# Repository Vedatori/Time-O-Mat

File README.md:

# Time-O-Mat [cz]
Time-O-Mat jsou hodiny navržené pro Letní robotický tábor 2022 organizovaný spolkem [Vědátoři](vedatori.com). Jedná se o otevřenou platformu, která si klade za cíle zlepšit dovednosti při mechanické stavbě a pájení. Účastníci dostali tento výrobek jako stavebnici, kdy z předem připravených dílů sestavili mechanickou část a poté pájeli nestandardní součástky na DPS s předem osazenými SMD součástkami. Po finalizaci je možné hodiny naprogramovat a používat pro zlepšení schopností algoritmizace a programování účastníků díky možnostem, které poskytují vsupní a výstupní periferie.

Mechanickou část lze rozdělit na dvě hlavní části - krabici a osmičky (segmentové zobrazovače). Vnější části krabice jsou vyřezány z překližky na laserové řezačce a obsahují zámkové západky. Ty se při stavbě lepí disperzním lepidlem a po vyschnutí tvoří pevný základ pro uložení ostatních dílů. Pouze horní část je odnímatelná a připevněná šrouby, které jsou schované v podpůrných 3D tištěných dílech, aby nekazily estetický dojem. Základní díl osmiček a dvojtečky je vytisknutý na 3D tiskárně a difuzery jednotlivých segmentů vyřezané z mléčného plexiskla se do něj vkládají z vnitřní strany a jsou uchyceny pomocí západek. Spojení osmiček a krabice zajišťuje 3D tištěný nosník umístěný uvnitř krabice, který také fixuje desky plošných spojů (DPS).

Hlavní DPS obsahuje zejména mikrokontroler ESP32, který je na ni připájen. Programování a napájení je zajištěno přes USB C. Hlavní DPS obsahuje také tlačítka, fotorezistory, bzučák a teplotní senzor. Do horního krytu je vsazena tenká podlouhlá DPS, která slouží jako senzor s osmi kapacitními tlačítky. Dominantou tohoto zařízení jsou DPS ve tvaru osmiček a dvojtečky, které jsou vsazeny za difuzery. Za každým segmentem jsou umístěny tři adresovatelné RGB LED. Další takové LED jsou umístěny zezadu na LED pásku, který zajišťuje ambientní podsvětlení prostoru za výrobkem. Hodiny jsou rozebiratelné, jednotlivé DPS jsou spojeny konektory, vzdálenější periferie pomocí kabelů.

Všechny periferie byly zvoleny tak, aby vytvořily hodiny s mnoha volitelnými postranními funkcionalitami. Díky nim je možné u účastníků tábora rozvíjet jejich schopnost algoritmizovat úlohu a programovat. Pro hodiny byla naprogramována softwarová knihovna, která výrazně zjednodušuje ovládání všech periferií. Pomocí této knihovny byl vytvořen vzorový software, který zobrazuje základní čas po připojení hodin na Wi-Fi. Po odpojení je poté čas uchován pomocí integrovaného RTC modulu, což umožňuje provoz hodin bez trvalého připojení k internetu. Hodiny je možné ovládat pomocí vstupních periferií nebo přes WiFi skrz počítač nebo smartphone, které přistupojí k interně hostované webové stránce. Všechny tyto vlastnosti lze přeprogramovat a přidat nové funkcionality podle přání vlastníka hodin. Zařízení se programuje ve Visual studio Code v jazyce c++ pomocí frameworku esp32-arduino.

Myšlenkou tohoto projektu je, aby Time-O-Mat tvořil každodenní užitečný doplněk pokoje, ale aby mohl být jeho software jednoduše modifikován a rozvíjen tak, jak si každý jeho vlastník představuje.

## Návod
Při stavbě hodin Time-O-Mat postupujte podle připravených návodů v následujícím pořadí:
1. [Návod pro elektroniku](https://github.com/vedatori/Time-O-Mat/blob/main/Manuals/Time-O-Mat_electronics_cz.md)
1. [Návod pro mechaniku](https://github.com/vedatori/Time-O-Mat/blob/main/Manuals/Time-O-Mat_mechanics_cz.md)
1. [Návod pro programování](https://github.com/vedatori/Time-O-Mat/blob/main/Manuals/Time-O-Mat_programming_cz.md)

# Time-O-Mat [en]
Time-O-Mat is a clock designed for Summer robotics camp 2022 (cz) organized by Vědátoři team (cz). It is a robotic platform offering development of mechanical assembly and soldering skills. The project has been designed as a kit for participants to be assembled and special electronic components to be soldered on a pre-assembled printed circuit board (PCB). When assembled it can be used to improve algorithmization and programming skills.

Mechanical set consists of two main parts - box and eights (segment displays). Box is made of laser cut plywood parts with latches that are mostly glued together. Upper parts are fastened using bolts hidden in inner 3D printed parts. The eights are 3D printed bodies with diffusers made of plexiglass clicked in them. Inner 3D printed parts ensure connection of the box and the eights.

Main PCB carries ESP32. It is programmed and powered using USB C and contains buttons, buzzer and photosensors. Capacitive touchbar with eight touch buttons is placed on upper part of the enclosure. Main eye-catcher of the clock is eight-shaped PCB with segments containing three adressable RGB LEDs in each segment. Ambient backlight is provided by LED strip on the backside of the clock. Clock can be disassembled if needed for upgrade or service and connectors are used for PCB interconnections.

All of the peripherals had been chosen to enrich the clock with various related functions. This enables development of algorithmization and programming skills of camp participants. Special internally developed software library makes programming of the clock much easier and allows better understanding of software features. Repository contains demo project that allows WiFi connection and time alignment of the clock with the Internet. Time is stored in RTC module after power off and it is not needed to establish WiFi connection after next power on. Clock can be controlled using input peripherals and Wi-Fi (using smartphone or PC) thru internally hosted website.

New features based on owner's needs can be easily introduced. Main aim of Time-O-Mat is to be a daily companion that offers easy software modifications and development.

## Licence
* Obsah tohoto repozitáře mimo složku *Software* je sdílen pod licencí [Attribution-NonCommercial-ShareAlike 4.0 International (CC BY-NC-SA 4.0)](https://creativecommons.org/licenses/by-nc-sa/4.0/).
* Obsah složky *Software* je sdílen pod licencí [GNU Lesser General Public License v3.0](https://www.gnu.org/licenses/lgpl-3.0.en.html).

## License
* The contents of this repository excluding folder *Software* is shared under license [Attribution-NonCommercial-ShareAlike 4.0 International (CC BY-NC-SA 4.0)](https://creativecommons.org/licenses/by-nc-sa/4.0/).
* The contents of the folder *Software* is shared under license [GNU Lesser General Public License v3.0](https://www.gnu.org/licenses/lgpl-3.0.en.html).

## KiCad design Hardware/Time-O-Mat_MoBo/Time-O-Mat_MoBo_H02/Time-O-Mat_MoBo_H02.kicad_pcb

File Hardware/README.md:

<h1>Designer's notes for Hardware development</h1>
<h2>USB C power supply current capability</h2>
The capability of each power supply can be determined by reading analog voltages on pins CC1 and CC2 connected to voltage dividers.

If the USB C standard in the cable and power adapter in use is properly implemented, one of the CC pins should always read 0V and the second one should be on one of the following voltage levels:
<ul>
  <li><strong>0,42V</strong> - legcy USB (1000mA most of the times)</li>
  <li><strong>0,94V</strong> - 1500mA</li>
  <li><strong>1,68V</strong> - 3000mA</li>
</ul>
The order of CC pins (e.g. if CC1 is 0V and CC2 is one of the three voltages or vice versa) is determined by the orientation of the cable and does not matter in our application.

<h2>To do list for next HW revision</h2>
<ul>
  <li>Zener diodes for power rails protection</li>
  <li>multi board wide power connector for testing</li>
  <li>add I2C header if possible</li>
  <li>buzzer pin spacing too wide</li>
  <li>Touch connector to JST, possibly without ground</li>
  <li>Fotorezistory - jeden na prostředek před dvojtečokou kolmo z desky, druhej ve stejné výčce</li>
  <li>lišta 240 mm</li>
  <li>díry 4 dolů a dvě mezi osmičky</li>
  <li>konektor na ws pásek k hraně</li>
  <li>reset possibly šroubovákem</li>
  <li>smdčka u segmentů bokem</li>

</ul>

<h2>To do list for next (H02) HW revision</h2>
<ul>
  <li>Add JST-XH connectors for the photoresistor in the back and backlight LED strip.</li>
  <li>Change touchbar graphics</li>
  <li>Lower supercapacitor resistor value</li>
  <li>Add 100k resistors in series between CC and Sensor V pins</li>
  <li>Maybye move the temperature sensor to the bottom</li>
  <li>Add LPF to photoresistor inputs</li>
  <li>Bigger Vedatori logo on the bottom, change to silk layer instead of copper.</li>
</ul>

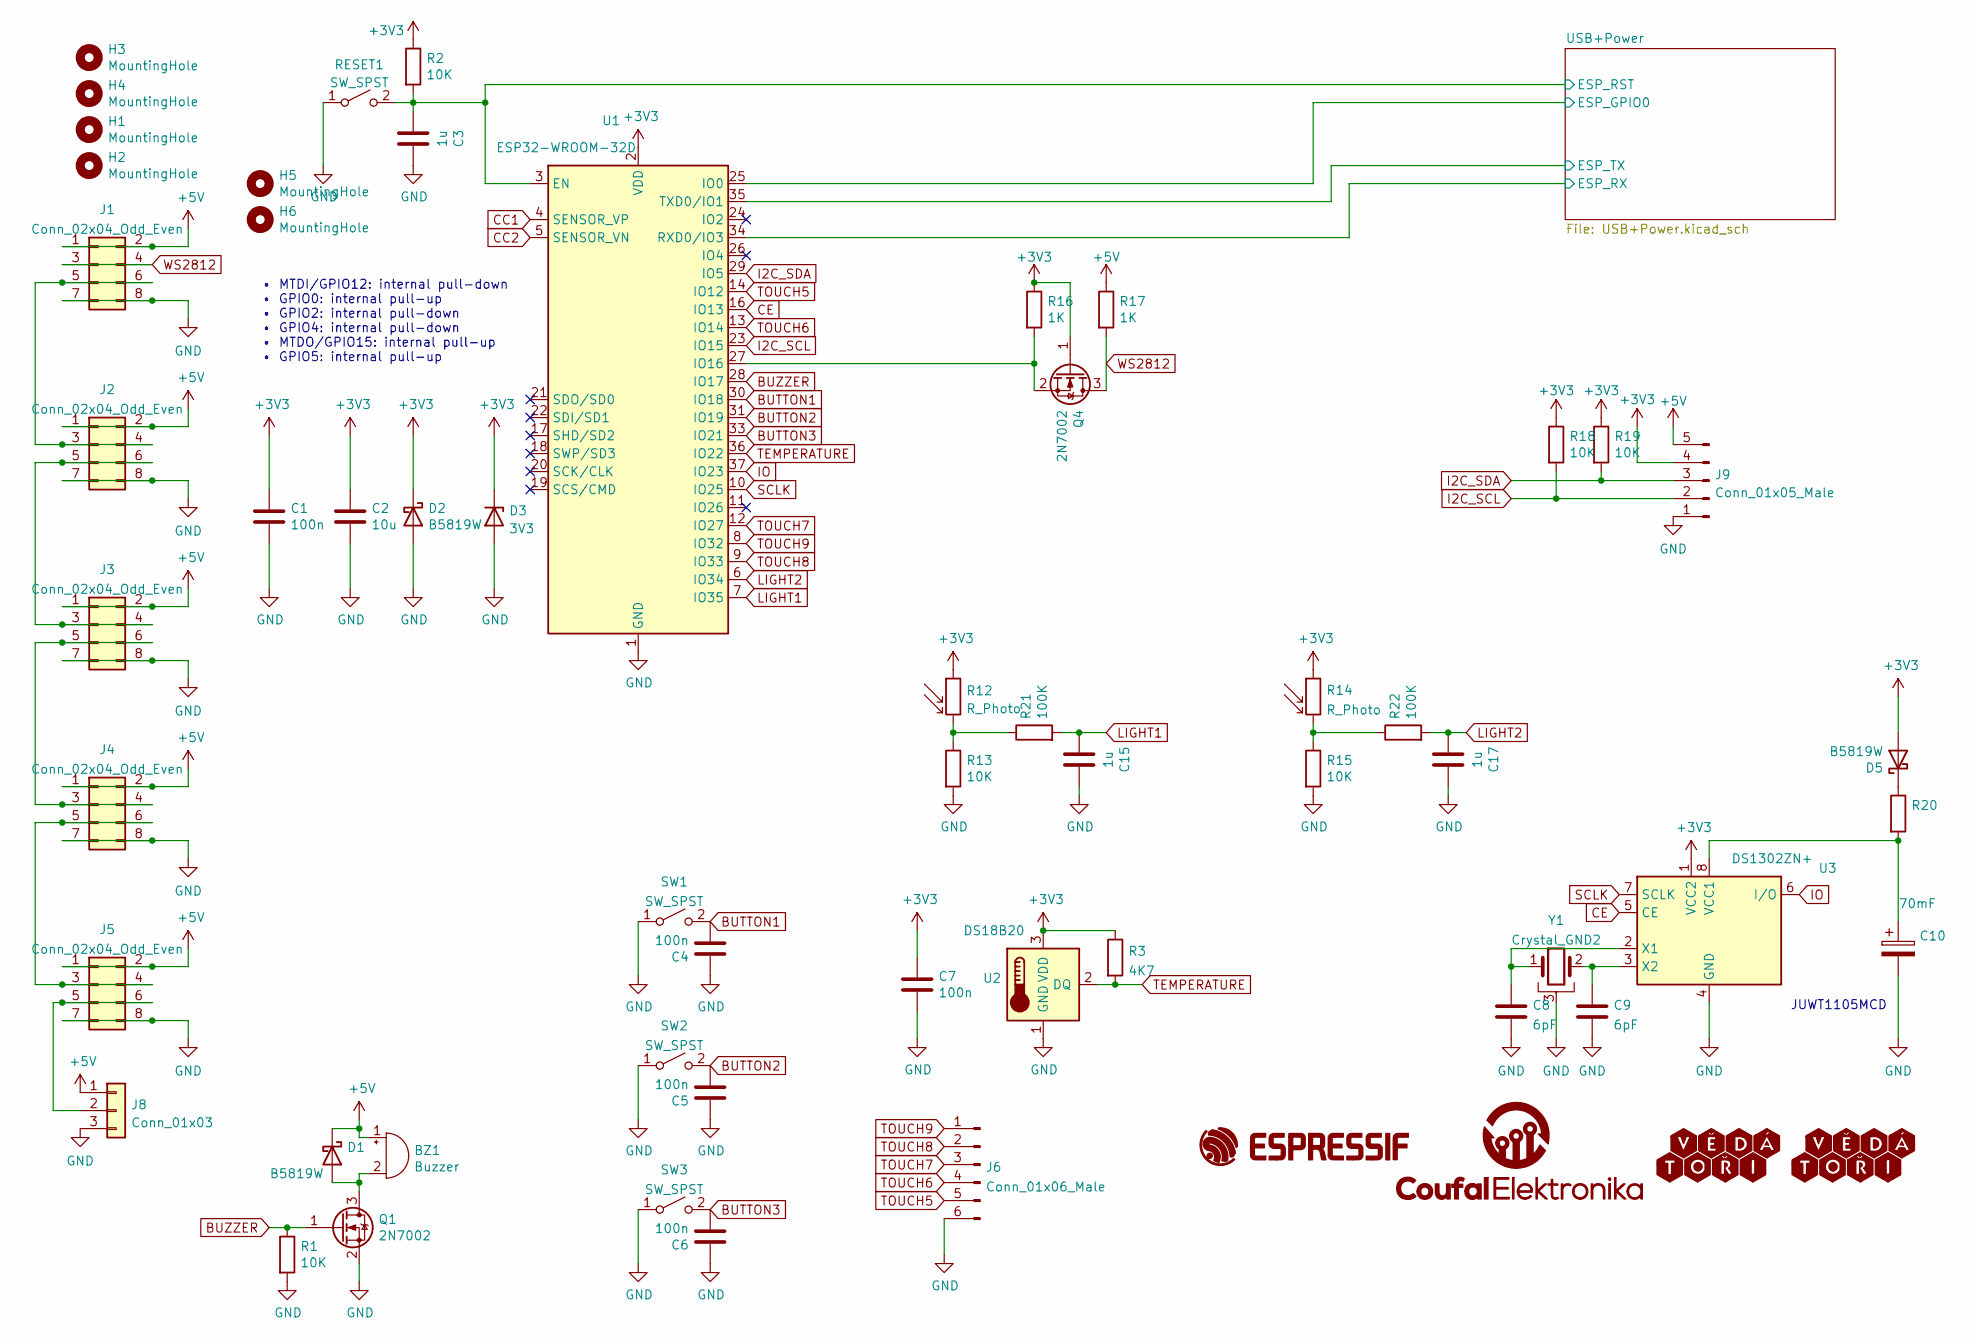
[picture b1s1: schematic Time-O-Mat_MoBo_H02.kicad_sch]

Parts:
BZ1: Buzzer; Buzzer_12x9.5RM6.6
C1, C4, C5, C6, C7: 100n; C_0603_1608Metric; LCSC C14663
C2: 10u; C_0805_2012Metric; LCSC C15850
C3, C15, C17: 1u; C_0603_1608Metric; LCSC C15849
C8, C9: 6pF; C_0603_1608Metric; LCSC C37474
C10: 70mF; SM3R3703T01U; LCSC C396469
D1, D2, D5: B5819W; D_SOD-123; LCSC C8598
D3: 3V3; D_MiniMELF; LCSC C8056
G1: CoufalElektronika_logo; Coufal_elektronika_text_30x13mm
G2: (no value)
G3: Vedatori_logo; Vedatori_15mm
G5: Espressif_logo; Espressif_logo_30mm
H1, H2, H3, H4, H5, H6: MountingHole; MountingHole_3.2mm_M3
J1, J2, J3, J4, J5: Conn_02x04_Odd_Even; PinHeader_2x04_P2.54mm_Vertical
J6: Conn_01x06_Male; JST_XH_B6B-XH-A_1x06_P2.50mm_Vertical
J8: Conn_01x03; JST_XH_S3B-XH-A-1_1x03_P2.50mm_Horizontal
J9: Conn_01x05_Male; PinHeader_1x05_P2.54mm_Vertical
Q1, Q4: 2N7002; SOT-23; LCSC C8545
R1, R2, R13, R15, R18, R19: 10K; R_0603_1608Metric; LCSC C25804
R3: 4K7; R_0603_1608Metric; LCSC C23162
R12: R_Photo; JST_XH_S2B-XH-A-1_1x02_P2.50mm_Horizontal
R14: R_Photo; R_LDR_5.1x4.3mm_P3.4mm_Vertical
R16, R17: 1K; R_0603_1608Metric; LCSC C21190
R20: LCSC C22859
R21, R22: 100K; R_0603_1608Metric; LCSC C25803
RESET1: SW_SPST; SW_SPST_TL3342; LCSC C318884
SW1, SW2, SW3: SW_SPST; SW_Tactile_SPST_Angled_PTS645Vx83-2LFS
U1: ESP32-WROOM-32D; ESP32-WROOM-32; LCSC C473012
U2: DS18B20; TO-92_HandSolder
U3: DS1302ZN+; SOIC-8_3.9x4.9mm_P1.27mm; LCSC C910859
Y1: Crystal_GND2; Crystal_DS26_D2.0mm_L6.0mm_Horizontal_1EP_style2

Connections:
+3V3: C1.1, C2.1, C7.1, D2.1 (K), D3.1 (K), D5.2 (A), J9.4, Q4.1 (G), R2.1, R3.1, R12.1, R14.1, R16.1, R18.1, R19.1, U1.2 (VDD), U2.3 (VDD), U3.1 (VCC2); also elsewhere on the board
+5V: BZ1.1 (-), D1.1 (K), J1.1, J1.2, J2.1, J2.2, J3.1, J3.2, J4.1, J4.2, J5.1, J5.2, J8.1, J9.5, R17.1; also elsewhere on the board
/USB+Power/ESP_GPIO0: U1.25 (IO0); also elsewhere on the board
/USB+Power/ESP_RST: C3.2, R2.2, RESET1.2 (B), U1.3 (EN); also elsewhere on the board
/USB+Power/ESP_RX: U1.34 (RXD0/IO3); also elsewhere on the board
/USB+Power/ESP_TX: U1.35 (TXD0/IO1); also elsewhere on the board
BUTTON1: C4.2, SW1.2 (B), U1.30 (IO18)
BUTTON2: C5.2, SW2.2 (B), U1.31 (IO19)
BUTTON3: C6.2, SW3.2 (B), U1.33 (IO21)
BUZZER: Q1.1 (G), R1.1, U1.28 (IO17)
CC1: U1.4 (SENSOR_VP); also elsewhere on the board
CC2: U1.5 (SENSOR_VN); also elsewhere on the board
CE: U1.16 (IO13), U3.5 (CE)
GND: C1.2, C2.2, C3.1, C4.1, C5.1, C6.1, C7.2, C8.2, C9.2, C10.2, C15.1, C17.1, D2.2 (A), D3.2 (A), J1.7, J1.8, J2.7, J2.8, J3.7, J3.8, J4.7, J4.8, J5.7, J5.8, J6.6, J8.3, J9.1, Q1.2 (S), R1.2, R13.2, R15.2, RESET1.1 (A), SW1.1 (A), SW2.1 (A), SW3.1 (A), U1.1 (GND), U1.15 (GND), U1.38 (GND), U1.39 (GND), U2.1 (GND), U3.4 (GND), Y1.3; also elsewhere on the board
I2C_SCL: J9.2, R18.2, U1.23 (IO15)
I2C_SDA: J9.3, R19.2, U1.29 (IO5)
IO: U1.37 (IO23), U3.6 (I/O)
LIGHT1: C15.2, R21.2, U1.7 (IO35)
LIGHT2: C17.2, R22.2, U1.6 (IO34)
unnamed: BZ1.2 (+), D1.2 (A), Q1.3 (D)
unnamed: C8.1, U3.2 (X1), Y1.1
unnamed: C9.1, U3.3 (X2), Y1.2
unnamed: C10.1, R20.2, U3.8 (VCC1)
unnamed: D5.1 (K), R20.1
unnamed: J1.5, J1.6, J2.3, J2.4
unnamed: J2.5, J2.6, J3.3, J3.4
unnamed: J3.5, J3.6, J4.3, J4.4
unnamed: J4.5, J4.6, J5.3, J5.4
unnamed: J5.5, J5.6, J8.2
unnamed: Q4.2 (S), R16.2, U1.27 (IO16)
unnamed: R12.2, R13.1, R21.1
unnamed: R14.2, R15.1, R22.1
SCLK: U1.10 (IO25), U3.7 (SCLK)
TEMPERATURE: R3.2, U1.36 (IO22), U2.2 (DQ)
TOUCH5: J6.5, U1.14 (IO12)
TOUCH6: J6.4, U1.13 (IO14)
TOUCH7: J6.3, U1.12 (IO27)
TOUCH8: J6.2, U1.9 (IO33)
TOUCH9: J6.1, U1.8 (IO32)
WS2812: J1.3, J1.4, Q4.3 (D), R17.2

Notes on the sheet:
JUWT1105MCD
• MTDI/GPIO12: internal pull-down • GPIO0: internal pull-up • GPIO2: internal pull-down • GPIO4: internal pull-down • MTDO/GPIO15: internal pull-up • GPIO5: internal pull-up

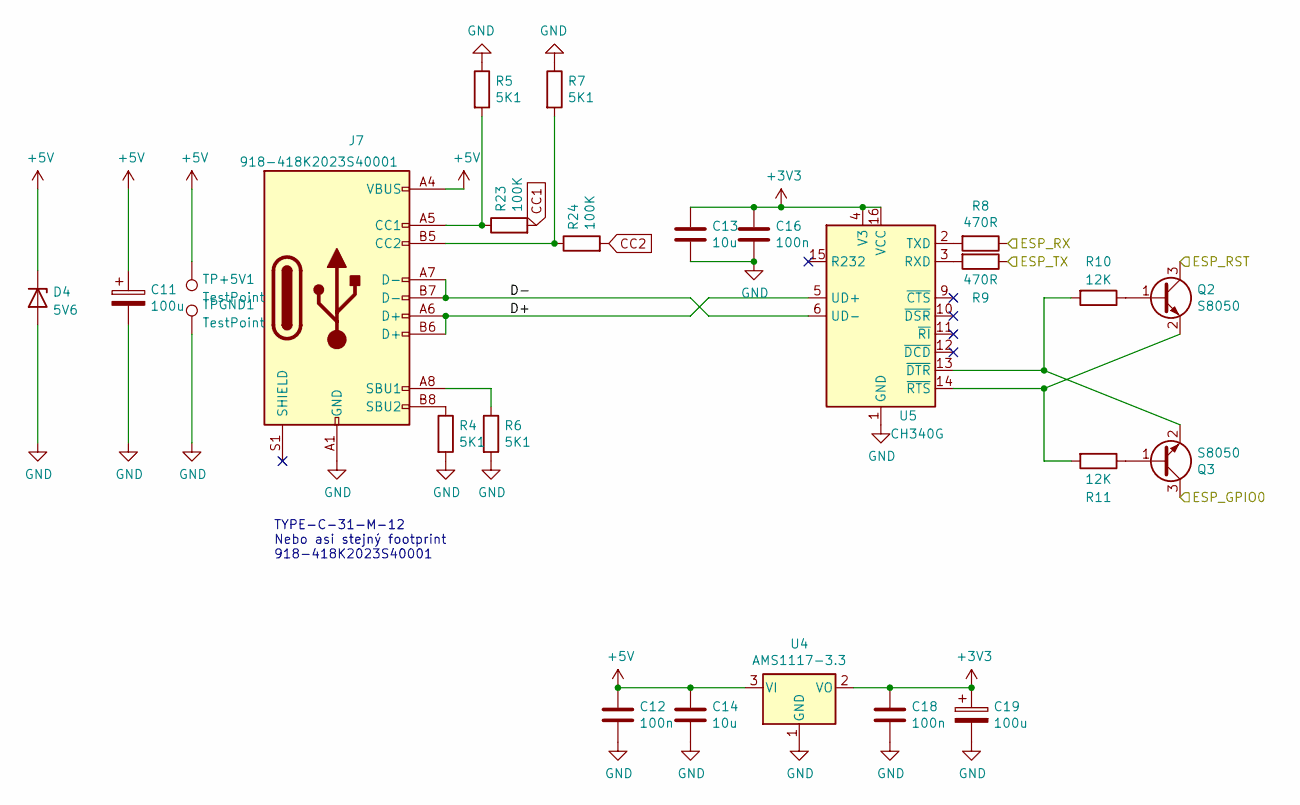
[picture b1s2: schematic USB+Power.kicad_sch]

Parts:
C11, C19: 100u; CP_Radial_D5.0mm_P2.00mm; LCSC C43803
C12, C16, C18: 100n; C_0603_1608Metric; LCSC C14663
C13: 10u; C_0603_1608Metric; LCSC C19702
C14: 10u; C_0805_2012Metric; LCSC C15850
D4: 5V6; D_MiniMELF; LCSC C8062
J7: 918-418K2023S40001; USB_C_Receptacle_HRO_TYPE-C-31-M-12; LCSC C167321
Q2, Q3: S8050; SOT-23; LCSC C2146
R4, R5, R6, R7: 5K1; R_0603_1608Metric; LCSC C23186
R8, R9: 470R; R_0603_1608Metric; LCSC C23179
R10, R11: 12K; R_0603_1608Metric; LCSC C22790
R23, R24: 100K; R_0603_1608Metric; LCSC C25803
TP+5V1: TestPoint; SolderWirePad_1x01_SMD_1x2mm
TPGND1: TestPoint; SolderWirePad_1x01_SMD_1x2mm
U4: AMS1117-3.3; SOT-223-3_TabPin2; LCSC C6186
U5: CH340G; SOIC-16_3.9x9.9mm_P1.27mm; LCSC C84681

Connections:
+3V3: C13.1, C16.1, C18.1, C19.1, U4.2 (VO), U5.4 (V3), U5.16 (VCC); also elsewhere on the board
+5V: C11.1, C12.1, C14.1, D4.1 (K), J7.A4 (VBUS), J7.A9 (VBUS), J7.B4 (VBUS), J7.B9 (VBUS), TP+5V1.1, U4.3 (VI); also elsewhere on the board
/USB+Power/D+: J7.A6 (D+), J7.B6 (D+), U5.5 (UD+)
/USB+Power/D-: J7.A7 (D-), J7.B7 (D-), U5.6 (UD-)
/USB+Power/ESP_GPIO0: Q3.3 (C); also elsewhere on the board
/USB+Power/ESP_RST: Q2.3 (C); also elsewhere on the board
/USB+Power/ESP_RX: R8.1; also elsewhere on the board
/USB+Power/ESP_TX: R9.1; also elsewhere on the board
CC1: R23.2; also elsewhere on the board
CC2: R24.2; also elsewhere on the board
GND: C11.2, C12.2, C13.2, C14.2, C16.2, C18.2, C19.2, D4.2 (A), J7.A1 (GND), J7.A12 (GND), J7.B1 (GND), J7.B12 (GND), R4.2, R5.1, R6.2, R7.1, TPGND1.1, U4.1 (GND), U5.1 (GND); also elsewhere on the board
unnamed: J7.A5 (CC1), R5.2, R23.1
unnamed: J7.A8 (SBU1), R6.1
unnamed: J7.B5 (CC2), R7.2, R24.1
unnamed: J7.B8 (SBU2), R4.1
unnamed: Q2.1 (B), R10.1
unnamed: Q2.2 (E), R11.2, U5.14 (~RTS)
unnamed: Q3.1 (B), R11.1
unnamed: Q3.2 (E), R10.2, U5.13 (~DTR)
unnamed: R8.2, U5.2 (TXD)
unnamed: R9.2, U5.3 (RXD)

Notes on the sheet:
TYPE-C-31-M-12 Nebo asi stejný footprint 918-418K2023S40001

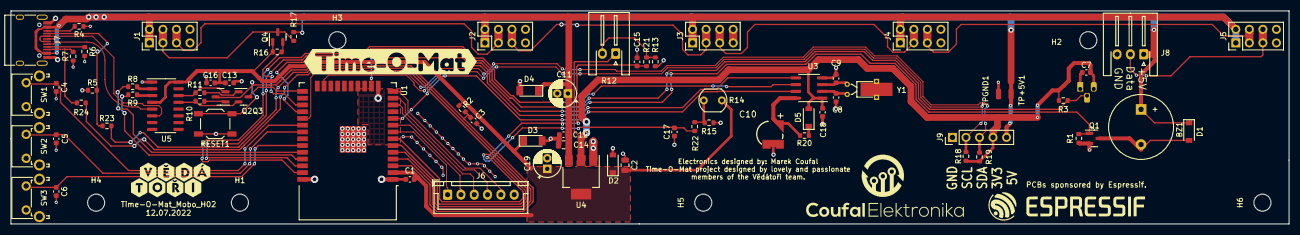
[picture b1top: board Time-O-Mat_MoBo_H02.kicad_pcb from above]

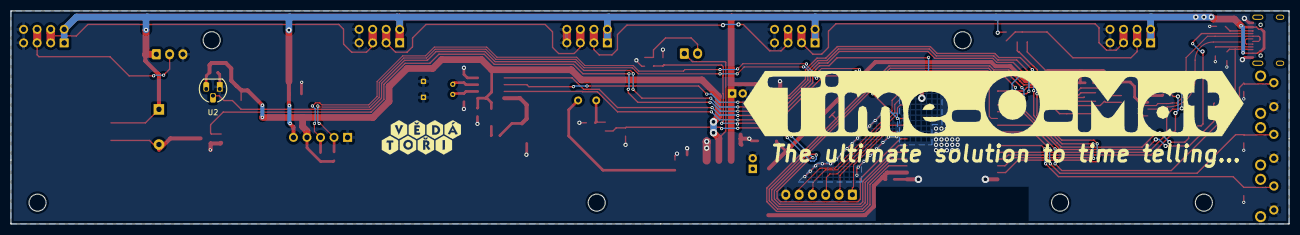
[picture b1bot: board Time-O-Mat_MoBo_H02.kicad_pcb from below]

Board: 2 copper layers, 240.0 x 40.0 mm, 86 parts (3 on the bottom side), 52 nets.

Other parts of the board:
kibuzzard-61E88A0E: G***; kibuzzard-61E88A0E
kibuzzard-61E8891A: G***; kibuzzard-61E8891A

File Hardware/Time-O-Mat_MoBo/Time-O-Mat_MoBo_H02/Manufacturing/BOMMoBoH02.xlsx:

Comment | Designator | Footprint | LCSC Part Number
100n | C1,C4,C5,C6,C7,C12,C16,C18 | Capacitor_SMD:C_0603_1608Metric | C14663
70mF | C10 | Time-O-Mat_Library:SM3R3703T01U | C396469
10u | C13 | Capacitor_SMD:C_0603_1608Metric | C19702
10u | C2,C14 | Capacitor_SMD:C_0805_2012Metric | C15850
1u | C3,C15,C17 | Capacitor_SMD:C_0603_1608Metric | C15849
6pF | C8,C9 | Capacitor_SMD:C_0603_1608Metric | C37474
B5819W | D1,D2,D5 | Diode_SMD:D_SOD-123 | C8598
3V3 | D3 | Diode_SMD:D_MiniMELF | C8056
5V6 | D4 | Diode_SMD:D_MiniMELF | C8062
918-418K2023S40001 | J7 | Connector_USB:USB_C_Receptacle_HRO_TYPE-C-31-M-12 | C167321
2N7002 | Q1,Q4 | Package_TO_SOT_SMD:SOT-23 | C8545
S8050 | Q2,Q3 | Package_TO_SOT_SMD:SOT-23 | C2146
10K | R1,R2,R13,R15,R18,R19 | Resistor_SMD:R_0603_1608Metric | C25804
12K | R10,R11 | Resistor_SMD:R_0603_1608Metric | C22790
1K | R16,R17 | Resistor_SMD:R_0603_1608Metric | C21190
10R | R20 | Resistor_SMD:R_0603_1608Metric | C22859
100K | R21,R22,R23,R24 | Resistor_SMD:R_0603_1608Metric | C25803
4K7 | R3 | Resistor_SMD:R_0603_1608Metric | C23162
5K1 | R4,R5,R6,R7 | Resistor_SMD:R_0603_1608Metric | C23186
470R | R8,R9 | Resistor_SMD:R_0603_1608Metric | C23179
SW_SPST | RESET1 | Button_Switch_SMD:SW_SPST_TL3342 | C318884
ESP32-WROOM-32D | U1 | RF_Module:ESP32-WROOM-32 | C473012
DS1302ZN+ | U3 | Package_SO:SOIC-8_3.9x4.9mm_P1.27mm | C910859
AMS1117-3.3 | U4 | Package_TO_SOT_SMD:SOT-223-3_TabPin2 | C6186
CH340G | U5 | Package_SO:SOIC-16_3.9x9.9mm_P1.27mm | C84681

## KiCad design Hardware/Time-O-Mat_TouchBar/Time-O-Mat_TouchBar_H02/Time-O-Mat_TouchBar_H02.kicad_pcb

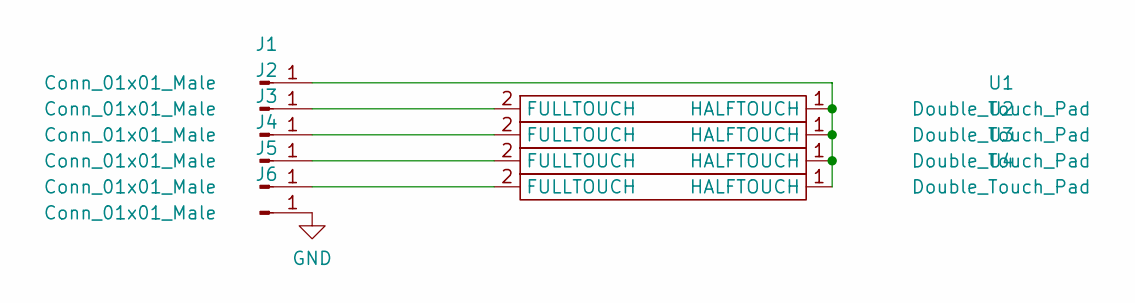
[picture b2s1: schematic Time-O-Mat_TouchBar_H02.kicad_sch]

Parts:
J1, J2, J3, J4, J5, J6: Conn_01x01_Male
U1, U2, U3, U4: Double_Touch_Pad; Double_Touchpad

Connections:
GND: J6.1
unnamed: J1.1, U1.1 (HALFTOUCH), U2.1 (HALFTOUCH), U3.1 (HALFTOUCH), U4.1 (HALFTOUCH)
unnamed: J2.1, U1.2 (FULLTOUCH)
unnamed: J3.1, U2.2 (FULLTOUCH)
unnamed: J4.1, U3.2 (FULLTOUCH)
unnamed: J5.1, U4.2 (FULLTOUCH)

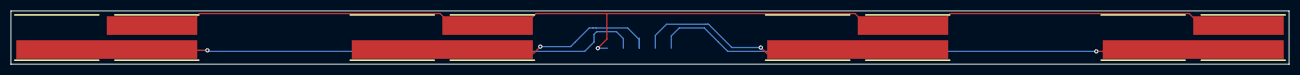
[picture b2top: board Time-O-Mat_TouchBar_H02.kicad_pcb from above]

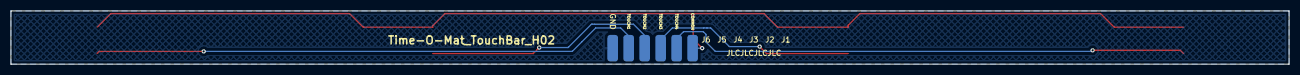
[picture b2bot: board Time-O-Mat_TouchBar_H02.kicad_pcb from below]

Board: 2 copper layers, 240.0 x 10.0 mm, 10 parts (6 on the bottom side), 5 nets.

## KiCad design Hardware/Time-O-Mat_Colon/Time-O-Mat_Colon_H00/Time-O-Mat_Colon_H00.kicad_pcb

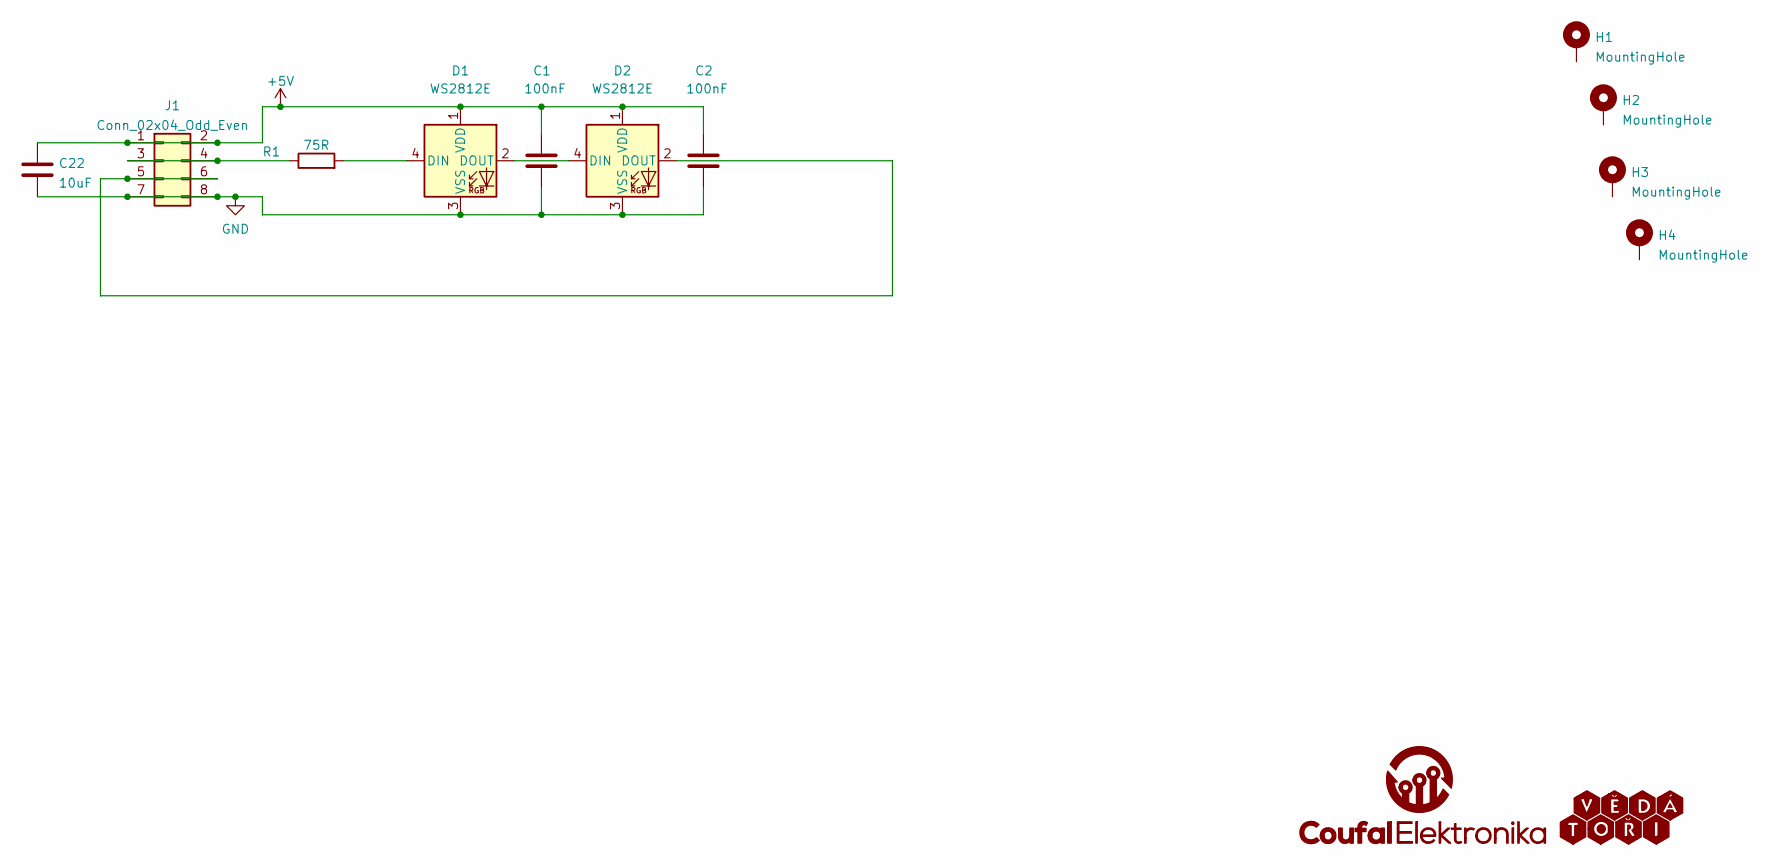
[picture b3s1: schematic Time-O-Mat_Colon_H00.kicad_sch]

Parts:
C1, C2: 100nF; C_0402_1005Metric; LCSC C1525
C22: 10uF; C_0603_1608Metric; LCSC C19702
D1, D2: WS2812E; LED_WS2812B_PLCC4_5.0x5.0mm_P3.2mm; LCSC C139127
G1: Vedatori_logo; Vedatori_15mm
G2: CoufalElektronika_logo; Coufal_elektronika_notext_10mm
H1, H2, H3, H4: MountingHole; MountingHole_3.2mm_M3_Pad_Via
J1: Conn_02x04_Odd_Even; PinSocket_2x04_P2.54mm_Horizontal
R1: 75R; R_0603_1608Metric; LCSC C4275

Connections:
+5V: C1.1, C2.1, C22.1, D1.1 (VDD), D2.1 (VDD), J1.1, J1.2
GND: C1.2, C2.2, C22.2, D1.3 (VSS), D2.3 (VSS), J1.7, J1.8
unnamed: D1.2 (DOUT), D2.4 (DIN)
unnamed: D1.4 (DIN), R1.2
unnamed: D2.2 (DOUT), J1.5, J1.6
unnamed: J1.3, J1.4, R1.1

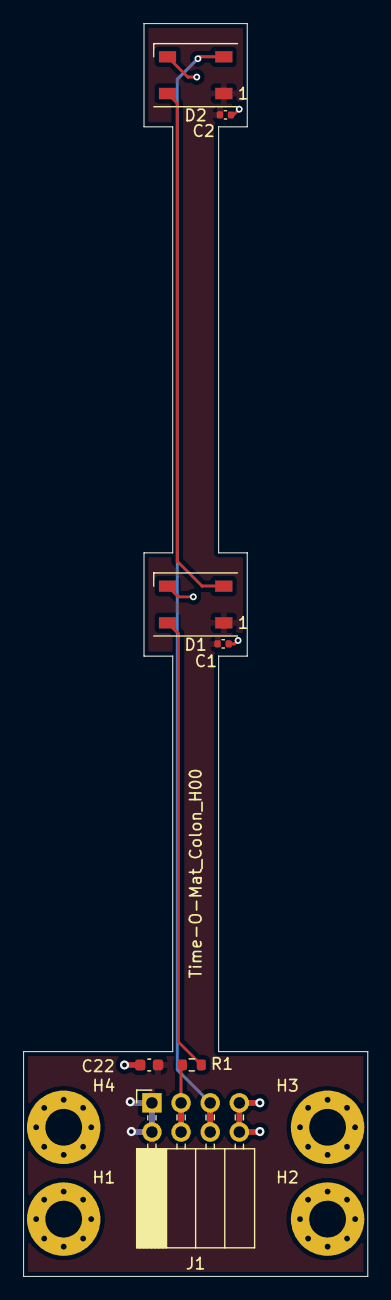
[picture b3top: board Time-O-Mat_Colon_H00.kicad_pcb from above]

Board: 2 copper layers, 30.0 x 109.2 mm, 12 parts (1 on the bottom side), 6 nets.

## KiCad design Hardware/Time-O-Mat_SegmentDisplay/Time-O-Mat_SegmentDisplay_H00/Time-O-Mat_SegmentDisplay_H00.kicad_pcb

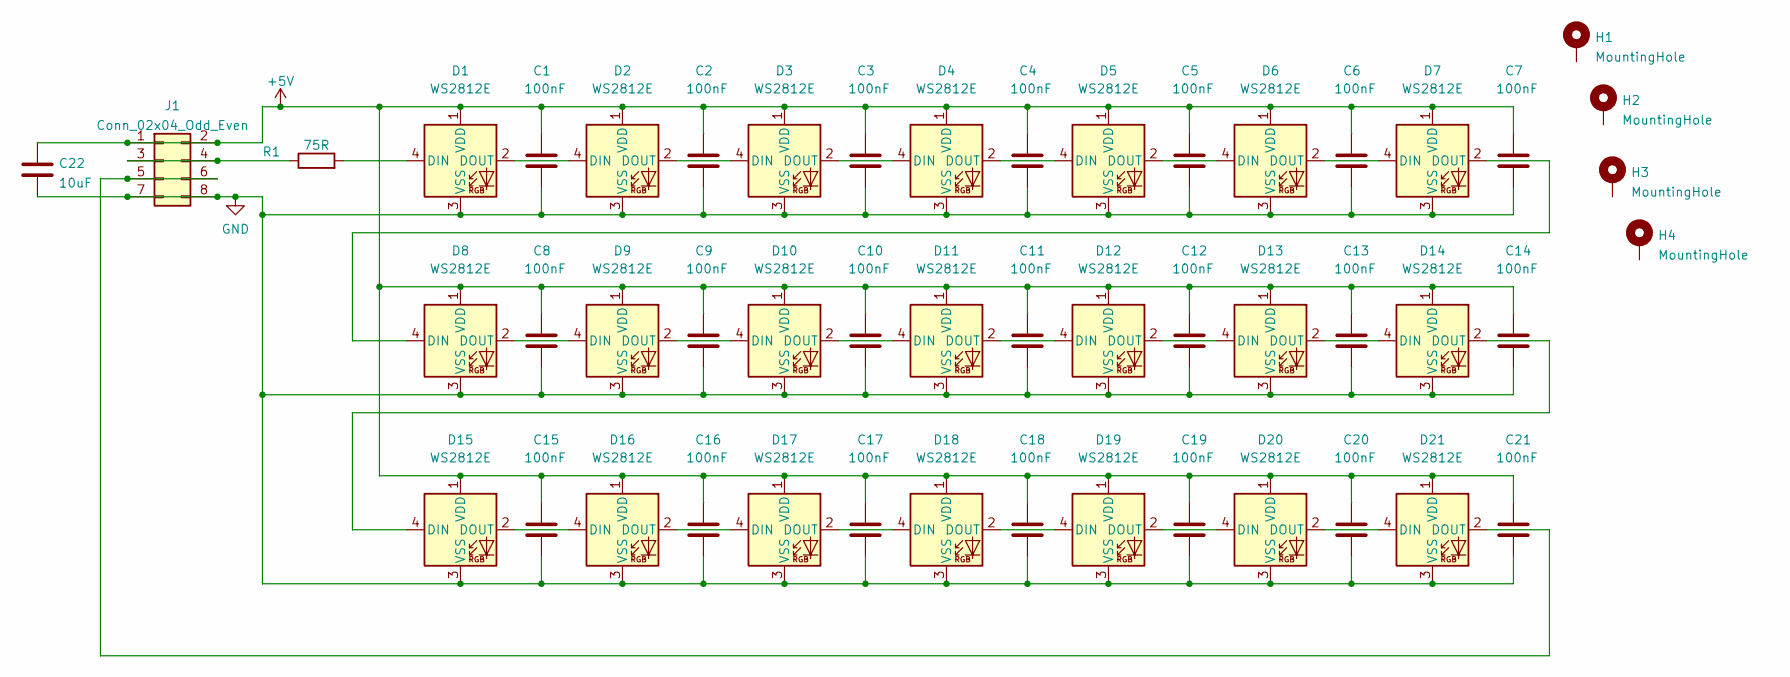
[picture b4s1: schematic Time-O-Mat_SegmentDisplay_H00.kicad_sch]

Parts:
C1, C2, C3, C4, C5, C6, C7, C8, C9, C10, C11, C12, C13, C14, C15, C16, C17, C18, C19, C20, C21: 100nF; C_0402_1005Metric; LCSC C1525
C22: 10uF; C_0603_1608Metric; LCSC C19702
D1, D2, D3, D4, D5, D6, D7, D8, D9, D10, D11, D12, D13, D14, D15, D16, D17, D18, D19, D20, D21: WS2812E; LED_WS2812B_PLCC4_5.0x5.0mm_P3.2mm; LCSC C139127
H1, H2, H3, H4: MountingHole; MountingHole_3.2mm_M3_Pad_Via
J1: Conn_02x04_Odd_Even; PinSocket_2x04_P2.54mm_Horizontal
R1: 75R; R_0603_1608Metric; LCSC C4275

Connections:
+5V: C1.1, C2.1, C3.1, C4.1, C5.1, C6.1, C7.1, C8.1, C9.1, C10.1, C11.1, C12.1, C13.1, C14.1, C15.1, C16.1, C17.1, C18.1, C19.1, C20.1, C21.1, C22.1, D1.1 (VDD), D2.1 (VDD), D3.1 (VDD), D4.1 (VDD), D5.1 (VDD), D6.1 (VDD), D7.1 (VDD), D8.1 (VDD), D9.1 (VDD), D10.1 (VDD), D11.1 (VDD), D12.1 (VDD), D13.1 (VDD), D14.1 (VDD), D15.1 (VDD), D16.1 (VDD), D17.1 (VDD), D18.1 (VDD), D19.1 (VDD), D20.1 (VDD), D21.1 (VDD), J1.1, J1.2
GND: C1.2, C2.2, C3.2, C4.2, C5.2, C6.2, C7.2, C8.2, C9.2, C10.2, C11.2, C12.2, C13.2, C14.2, C15.2, C16.2, C17.2, C18.2, C19.2, C20.2, C21.2, C22.2, D1.3 (VSS), D2.3 (VSS), D3.3 (VSS), D4.3 (VSS), D5.3 (VSS), D6.3 (VSS), D7.3 (VSS), D8.3 (VSS), D9.3 (VSS), D10.3 (VSS), D11.3 (VSS), D12.3 (VSS), D13.3 (VSS), D14.3 (VSS), D15.3 (VSS), D16.3 (VSS), D17.3 (VSS), D18.3 (VSS), D19.3 (VSS), D20.3 (VSS), D21.3 (VSS), J1.7, J1.8
unnamed: D1.2 (DOUT), D2.4 (DIN)
unnamed: D1.4 (DIN), R1.2
unnamed: D2.2 (DOUT), D3.4 (DIN)
unnamed: D3.2 (DOUT), D4.4 (DIN)
unnamed: D4.2 (DOUT), D5.4 (DIN)
unnamed: D5.2 (DOUT), D6.4 (DIN)
unnamed: D6.2 (DOUT), D7.4 (DIN)
unnamed: D7.2 (DOUT), D8.4 (DIN)
unnamed: D8.2 (DOUT), D9.4 (DIN)
unnamed: D10.2 (DOUT), D11.4 (DIN)
unnamed: D9.2 (DOUT), D10.4 (DIN)
unnamed: D11.2 (DOUT), D12.4 (DIN)
unnamed: D12.2 (DOUT), D13.4 (DIN)
unnamed: D13.2 (DOUT), D14.4 (DIN)
unnamed: D14.2 (DOUT), D15.4 (DIN)
unnamed: D15.2 (DOUT), D16.4 (DIN)
unnamed: D16.2 (DOUT), D17.4 (DIN)
unnamed: D17.2 (DOUT), D18.4 (DIN)
unnamed: D18.2 (DOUT), D19.4 (DIN)
unnamed: D19.2 (DOUT), D20.4 (DIN)
unnamed: D20.2 (DOUT), D21.4 (DIN)
unnamed: D21.2 (DOUT), J1.5, J1.6
unnamed: J1.3, J1.4, R1.1

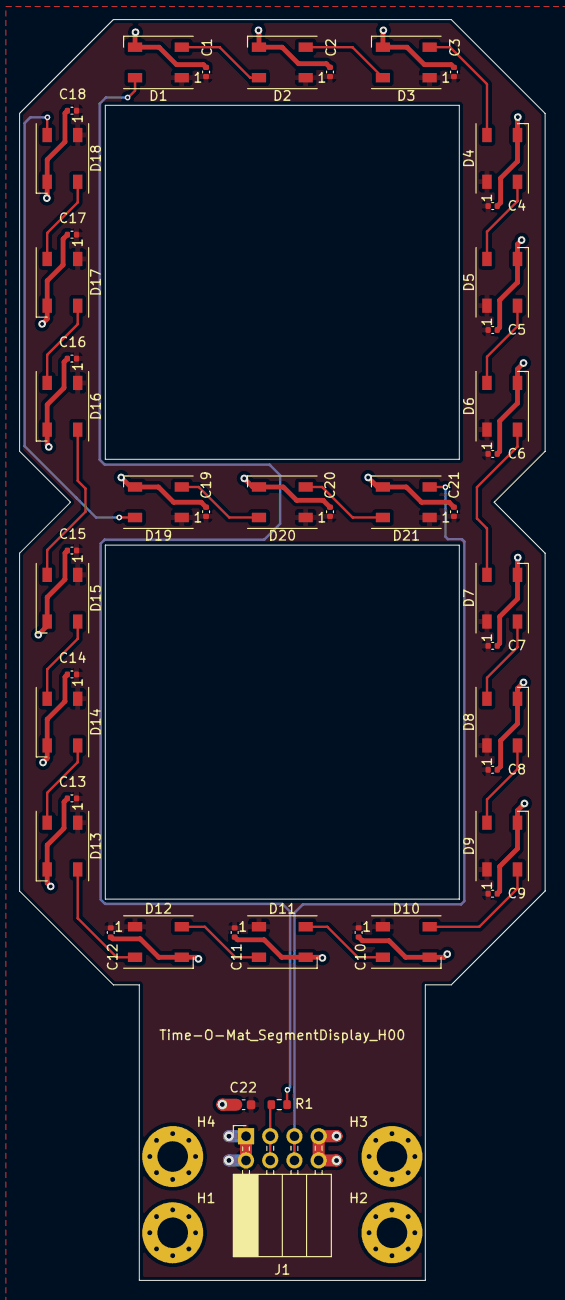
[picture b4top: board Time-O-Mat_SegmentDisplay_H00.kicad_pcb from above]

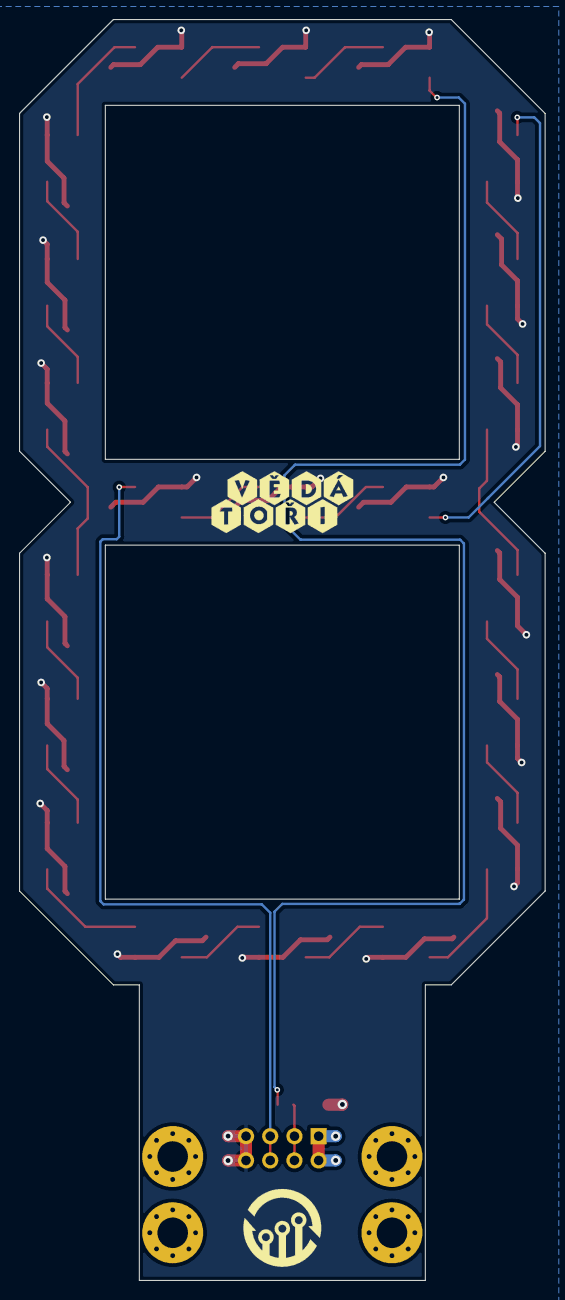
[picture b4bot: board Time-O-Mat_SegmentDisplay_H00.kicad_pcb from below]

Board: 2 copper layers, 55.1 x 132.3 mm, 51 parts (2 on the bottom side), 25 nets.

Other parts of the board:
G1: Vedatori_logo; Vedatori_15mm
G2: CoufalElektronika_logo; Coufal_elektronika_notext_10mm

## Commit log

2022-01-15 Add license information
2022-01-15 First Hardware commit
2022-01-15 Created segment PCB
2022-01-15 Exported step model with components
2022-01-15 Updated segment pcb
2022-01-16 PCB updates
2022-01-16 HW update
2022-01-16 Colon update
2022-01-19 HW updates
2022-01-19 HW updates.
2022-02-15 Exported up to date STEP models and manufacturing data
    Exported up to date 3D models of all PCB parts.
    Created new subpanels fot manufacturing to counteract duplicit designators on different boards.
2022-02-16 Added H00 PCB panel screenshot to Readme.
2022-03-01 HW designers notes.
2022-03-24 Tested HW components
    Photoresistor missing
2022-03-29 Basic ntp clock demo. Displaying characters and short text on the display.
2022-03-29 Checking characters range for display.
2022-04-07 Updating leds synchronously. Added color definitions.
2022-05-26 Update HW to do list
2022-05-31 H01 changes
2022-05-31 H01 touchbar updates
2022-06-25 H01 manufacaturing changes
2022-06-25 Added CC and Light pins Readout to Serial
2022-06-27 Controlling display brightness.
2022-06-27 First version of linear display transitions.
2022-06-28 Fixed linear transition stable state. Setting brightness once.
2022-07-08 Updarted HW Readme
    Added ToDo list for H02.
2022-07-09 RGB and HSV color representation. Fixed LED linear transition. Reindexed LED segments.Controlling backlight.
2022-07-12 H02 commits
2022-07-12 H02 updates
2022-07-12 Exported manufacturing data
2022-07-13 H02 changes
2022-07-13 Final HW changes
2022-07-14 experimental hue and value changes
2022-07-16 Mechanical manual draft added
    Mechanical manual without photos, needs review
2022-07-20 Display polling in hidden lib task. DS18B20 moved to lib.
2022-08-05 Electronics manual.
2022-08-05 Fix chapter name.
2022-08-06 Manuals update
    Photos added to Mechanics manual, manual optimised. Minor changes in Electronics manual.
2022-08-10 Manual update
    Photoresistor, LED strip and touchbar added to Electronics manual.
2022-08-11 Corrections in electronics manual.
2022-08-11 Small corrections to mechanics manual.
2022-08-11 Set theme jekyll-theme-slate
2022-08-11 Electronics manual new format test.
2022-08-11 Reformatted mecha and electro manual. Small mecha manual corrections.
2022-08-12 Time module created.
2022-08-12 Added buttons and touchbar module to TM lib.
2022-08-13 Added USB power limit module.
2022-08-13 Added illumination module.
2022-08-13 Renamed time-o-mat class and object.
2022-08-13 Printing diagnostic info via lib function.
2022-08-13 test pages in docs
2022-08-13 Added limited version of WiFiCaptain
2022-08-14 Added sanding plexi glass step.
2022-08-14 Before-mecha cleanup.
2022-08-14 Cleanup after sanding.
2022-08-15 First programming manual.
2022-08-15 Updated OneWire to 2.3.7
2022-08-15 Integrated piezo lib from Intermodules temporarily.
2022-08-15 Ficed structure of prog. manual.
2022-08-15 Updated prog. manual up to buttons.
2022-08-15 Programming lectures and challenges draft added
2022-08-15 Reading temperature + in manual.
2022-08-15 Fixed photoresistor pins.
2022-08-15 Minor update
2022-08-15 Digital touchbar output. Turning leds off after start.
2022-08-16 TouchBar manual added
2022-08-16 Fixed InterModules/piezo
2022-08-16 Fixed piezo lib
2022-08-16 COde addet for first three lectures
2022-08-16 Moved connecting disp to ToMat lib.
2022-08-16 Allow display to show space/empty char
2022-08-16 Fixed showing 0 at the start
2022-08-16 Fixed transition not working properly
2022-08-16 Revert Time_module.cpp
2022-08-16 Revert "Fixed transition not working properly"
    This reverts commit 34e1afa761425f0595a71d690200539841f6d081.
2022-08-16 Added display section to prog. manual.
2022-08-16 Lecture 4 added
2022-08-17 Update backlight api.
2022-08-17 Fixed touchbar filter.
2022-08-17 Touchbar update
2022-08-17 Fix digit indexes.
2022-08-18 Moved display.update into separate task & updated manuals.
2022-08-18 Moved illumination updates to quicker task.
2022-08-18 Lecture 5 added
2022-08-18 Fixed display refresh without wifi.
2022-08-19 Added ping library
2022-08-19 Added json library
2022-08-19 Added weatherApi
2022-08-19 Some fixes to Weather
2022-08-19 Added theme melody, fixed main.cpp
2022-08-19 Update power api.
2022-08-19 Moved display updates into display module.
2022-08-19 Weather api web config
2022-08-19 Updating panel brightness automatically.
2022-08-19 Fixed c_strings
2022-08-19 Refactored integration of weatherApi to ToMat. Added default location to Choteborky.
2022-08-19 Disabling softAP 5 minutes after connected to internet.
2022-08-19 Added default option for setting api key and pos
2022-08-19 touchBar getPressedIndex() function.
2022-08-19 Fixed disabling softAP when wifiCapt not started.
2022-08-20 Added ErriezDS1302 library
2022-08-20 Mechanical files added
    .stl, .dxf and .svg files added.
2022-08-20 Time module now uses RTC
2022-08-23 Added examples.
2022-09-06 Setting display transitions separately for front and back. Inversed transition rate parameter.
2022-09-14 Restructured display segments control, brightness and transition settings.
2022-09-14 Fixed roulette demo.
2022-10-08 Readme added
    CZ and EN version
2022-10-08 readme form fix
2022-10-13 Added ping servers to check for internet connection.
2022-10-20 Time module rework
2022-10-21 Revert "Time module rework"
    This reverts commit 9a64cf988bfc1bbdb4341091c141d592ec8ff98f.
2022-10-30 Fixed NTP summer time offset. Added manual time settings. Added front display color settings.
2022-11-08 color setting command added
2022-11-08 r, g, b declaration moved and description added to manual
2022-11-08 Color values to int type. Altered menual.
2022-12-26 Fixed int to uint8_t conversion in wifi command.
2023-01-03 Fix prog manual images.
2023-01-30 Added manual setting time via web app.
2023-01-31 Disabled colon blinking by default.
2023-01-31 Updated Adafruit_Neopixel Lib to 1.10.7
2023-02-03 Fixed espressif32 platform.
2023-02-10 Added readme pictures of ToMat.
2023-02-10 Fixed headings in readme.
2023-02-21 LED states as structs
2023-03-18 Fixed brightness and transition setters.
2023-03-19 Fixed linear transition to move in target color direction.
2023-03-19 Function converting RGB to HSV format.
2023-03-30 Exponential transition operational
2023-03-31 Updating LEDs only when necessary.
2023-03-31 Power module automatic mode
2023-04-01 Updating time zone codes using webApp commands.
2023-04-10 Limiting LED current.
2023-04-11 Added power limit to prog. manual. transRate -> transTime.
2023-04-12 Fix idle current const. Refactored main loop.
2023-04-13 Fix idle current. Narrowed exp. transition. Printing diagnostics.
2023-04-13 Add demo SW tutorial
2023-04-14 Fixed colon color updating.
2023-05-17 Basic MQTT LED control demo.
2023-05-17 WiFi reconnection hotfix.
2023-05-18 Improved default back light color.
2023-06-01 Added TextMode parameter for displaying text or char.
2023-08-16 Removed leading "0" symbol from time display.
